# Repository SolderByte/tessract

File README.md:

# tessract

### BOM:
* x3 47 Ohm resistors
* x1 330 Ohm resistor
* x2 10k Ohm resistor
* x1 100k Ohm resistor
* x2 10 uF Capacitor
* x2 .1 uF Capacitor
* x1 4.7 uF Capacitor
* x1 Push button switch
* x1 LED
* x1 Li-Ion Battery
* x1 Micro USB
* x1 ATMEL ATtiny85
* x1 Microchip MCP73832
* x1 Microchip MCP1755 (MIC5504 alternative)
* x1 Osram LRTB GFTG

### Current consumption:

| Part | Current |
|---|---|
| ATMEL ATtiny85 | 3mA = 3.3V @ 8MHz, 5mA = 5V @ 8MHz |
| HM-10  | 50mA = 3.3V (active 8.5mA, sleep 50-200uA)  |
| OSRAM LRTB GFTG  | Red = 5-40mA, Green = 5-50mA, Blue = 5-50mA  |

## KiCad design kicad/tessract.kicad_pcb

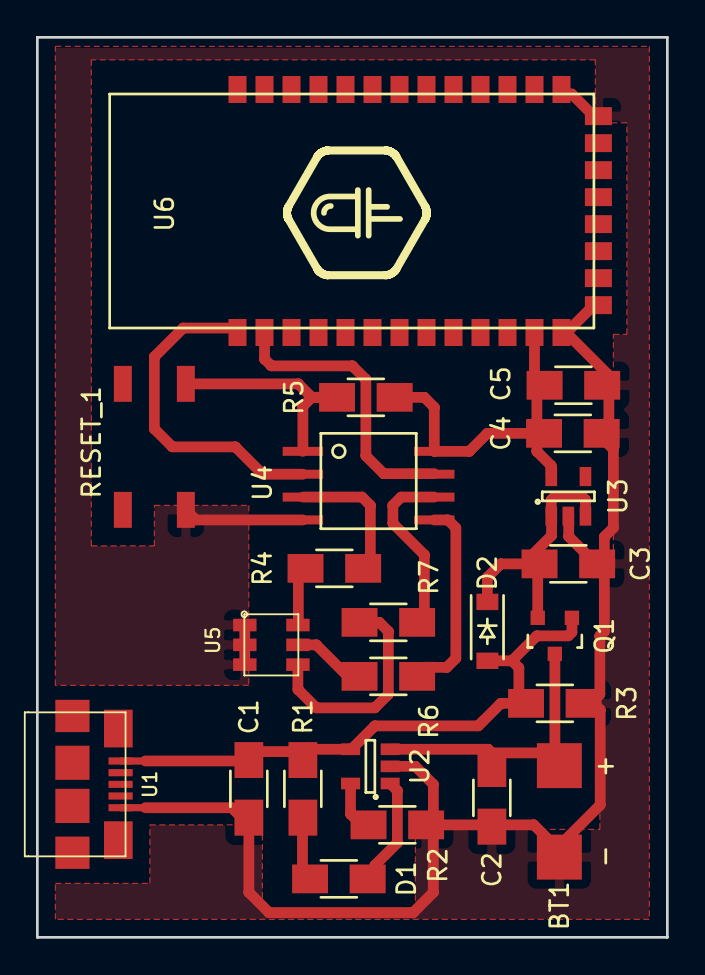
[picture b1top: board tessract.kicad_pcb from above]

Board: 2 copper layers, 35.0 x 50.0 mm, 25 parts (1 on the bottom side), 17 nets.

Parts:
BT1: Battery; SMD_BATT
C1, C3: 10uF; SMD_1206
C2: 4.7uF; SMD_1206
C4, C5: .1uF; SMD_1206
D1: LED; SMD_1206
D2: B130LAW; SOD_123
Q1: DMP1045U; SOT_23
R1: 330; SMD_1206
R2, R5: 10k; SMD_1206
R3: 100k; SMD_1206
R4, R6, R7: 47; SMD_1206
RESET_1: SW_PUSH; TL3305_SWITCH
U1: MICRO_B_USB
U2: MCP73832T; SOT_23_5
U3: MCP1755; SOT_23_5
U4: ATMEL_ATTINY85_20SU; SOIC8_EIAJ_208MIL
U5: OSRAM_LRTB_GFTG; OSRAM_RGB_LED
U6: HM-10
solderbyte_logo: G***; solderbyte_logo_25mm
solderbyte_logo#2: G***; SOLDERBYTE_LOGO_20MM

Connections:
Earth: BT1.2, C1.2, C2.2, C3.2, C4.2, C5.2, R2.2, R3.1, RESET_1.1, U1.5, U2.2, U3.2, U4.4, U5.1, U5.2, U5.3, U6.13, U6.14, U6.21, U6.22
unnamed: BT1.1, C2.1, Q1.3, U2.3
unnamed: C1.1, D2.2, Q1.1, R1.1, R3.2, U1.1, U2.4
unnamed: C3.1, D2.1, Q1.2, U3.1, U3.3
unnamed: C4.1, C5.1, R5.1, U3.5, U4.8, U6.12
unnamed: D1.1, U2.1
unnamed: D1.2, R1.2
unnamed: R2.1, U2.5
unnamed: R4.1, U5.6
unnamed: R4.2, U4.3
unnamed: R5.2, RESET_1.2, U4.1
unnamed: R6.1, U5.5
unnamed: R6.2, U4.5
unnamed: R7.1, U5.4
unnamed: R7.2, U4.6
unnamed: U4.2, U6.1
unnamed: U4.7, U6.2

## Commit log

2016-10-17 kicad project
2016-10-17 kicad libs
2016-10-19 solderbyte library
2016-10-20 lib cleanup
2016-10-20 remove dcm
2016-11-01 setting up schematic
2016-11-10 added mcp1755 and mosfet
2016-12-05 schematic draft
2016-12-20 add footprints
2016-12-30 add pcb layout
2017-01-01 copper plane
2017-01-13 organize silkscreen
2017-01-17 wider track and silkscreen logo
2017-01-31 removed library
2017-02-21 arduino and android first pass
2017-02-26 android shutdown receiver
2017-02-27 android bluetooth scan
2017-03-06 adroid bluetooth paired
2017-03-06 android bluetooth connect
2017-03-07 android connect dialog
2017-03-14 android application list
2017-03-21 android json intents
2017-03-23 android app list progress
2017-03-26 android icon app list
2017-03-27 android json store
2017-03-29 android color picker xml
2017-03-30 android color picker seekbar
2017-03-31 android color picker update view
2017-04-04 android fixed color picker cursor
2017-04-05 android color picker save and remove from application list
2017-04-07 android app list with color
2017-04-11 android progress dialog applications
2017-04-11 android rearrange code
2017-04-12 android disconnect bluetooth
2017-04-18 android get notification data
2017-04-19 android get notification data from view
2017-04-23 android merge notification json objects
2017-04-24 arduino test and protocol
2017-04-24 android protocol
2017-04-25 android color to hex
2017-05-02 android dialog color class and device activity
2017-06-13 work in progress
